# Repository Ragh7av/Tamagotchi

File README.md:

<h1 align="center">Tamagotchi</h1>

<div align="center">         
<p align="center">
Super smol tamagotchi pet for you!
</p>

<h1 align="center">Overview</h1>
        
<p align="center">
 
 Custom tamagotchi with a super small formfactor and can help you [larp](https://en.wiktionary.org/wiki/LARP) building hardware. Made using the good old ESP32 C3 Supermini, an 0.96 oled panel, three [smol](https://en.wiktionary.org/wiki/smol) tactile switches, buzzer, and a battery [ofc](https://en.wikipedia.org/wiki/OFC) with a custom PCB and a 3D printed case! 

 [Onshape 3D Model link](https://cad.onshape.com/documents/aaa376a98daf92ea29d656f5/w/34884ae89482b25306f22cdd/e/82753004b14a47683b19c43f)

 #  Schematic

# Printed Circuit Board (PCB)

# 3D MODEL OF ASSEMBLY

# ZINE

<h1 align="center">Why did I even build this?</h1>
<p align="center">
 
 to [larp](https://en.wiktionary.org/wiki/LARP) as a super smol cyberpet is cool [asf](https://en.wikipedia.org/wiki/Autism_Science_Foundation). 
 
 </p>

<h1 align="center">The Features</h1>
</div>

**Feeding:** Fills the hunger meter (much like a crunchy kfc) with sound effects

**Playing:** Yooo... Pauses the normal world to launch the falling-item arcade game. Catching items makes the pet superrrr happy but sadlyy acts as a 20% battery tax on its energy.

**Sleeping:** Dims the screen into a snoozee/ sleeping mode, locking the controls until its energy battery safely recharges back to 100% and get's into full powerr.

# The Components Used

1. ESP32 C3 supermini.
2. 0.96-inch OLED Display (SSD1306)
3. smol Buzzer.
4. 6mm x 6mm x 8mm Tactile Switches (x3).
5. Battery
7. Custom designes PCB.
8. Custom 3D Printed Case.

# How to Build it?
## 1. Project Files and Parts
Download the necessary files from this repository:
* Gerbers: For ordering the custom PCB.
* 3D Prints: For printing the outer case.
* Firmware: For the Arduino source code.

Now collect all the hardware components. You will need an ESP32-C3 Supermini, a 0.96-inch I2C OLED display, three 6mm tactile switches, a buzzer and a battery cell.
## 2. Hardware Assembly

To assemble the hardware follow these steps:
1. Solder the ESP32-C3 Supermini onto the designated footprint on your PCB.
2. Next solder the three switches into positions SW4, SW5 and SW6.
3. Then solder the OLED display into the U2 slot.
4. After that solder the buzzer to the BZ1 pads.
5. Solder the battery wires to the BT1 power pads. It is very important to check the schematic to ensure the positive and negative match exactly to prevent shorting out the ESP32-C3 Supermini board.
6. Finally, Place the PCB in the 3D printed bottom case and screw it to the case.

## 3. Software Environment Setup

To set up the software environment follow these steps:

1. Install the Arduino IDE on your computer.
3. Go to File then Preferences. Add the official ESP32 library URL to the Additional Boards Manager URLs box.
5. Open Tools, Board then Boards Manager, search for ESP32 by Expressif and click install.
6. Go back to Tools, Board, then ESP32 Arduino and select ESP32 C3 Dev Module.

## 4. Library Installation and Flashing

To install the library and flash the firmware follow these steps:

1. Go to Sketch Include Library then Manage Libraries.
2. Search for Adafruit SSD1306. Click install. Select "Install All" to include the required Adafruit GFX dependency.
3. Open your project firmware file in the Arduino IDE.
4. Connect the ESP32-C3 Supermini device to your computer using a data cable.
5. Select the devices connection port, under Tools, Port.
6. Click the Upload button. The OLED screen will boot up with the system text soon as the terminal finishes writing the code to the ESP32-C3 Supermini.
   
<h1>Inspirations & Credits</h1> 
Huge thanks to the <strong>Fallout Hack Club Tamagotchi guide</strong> for the base inspiration and logic outline.

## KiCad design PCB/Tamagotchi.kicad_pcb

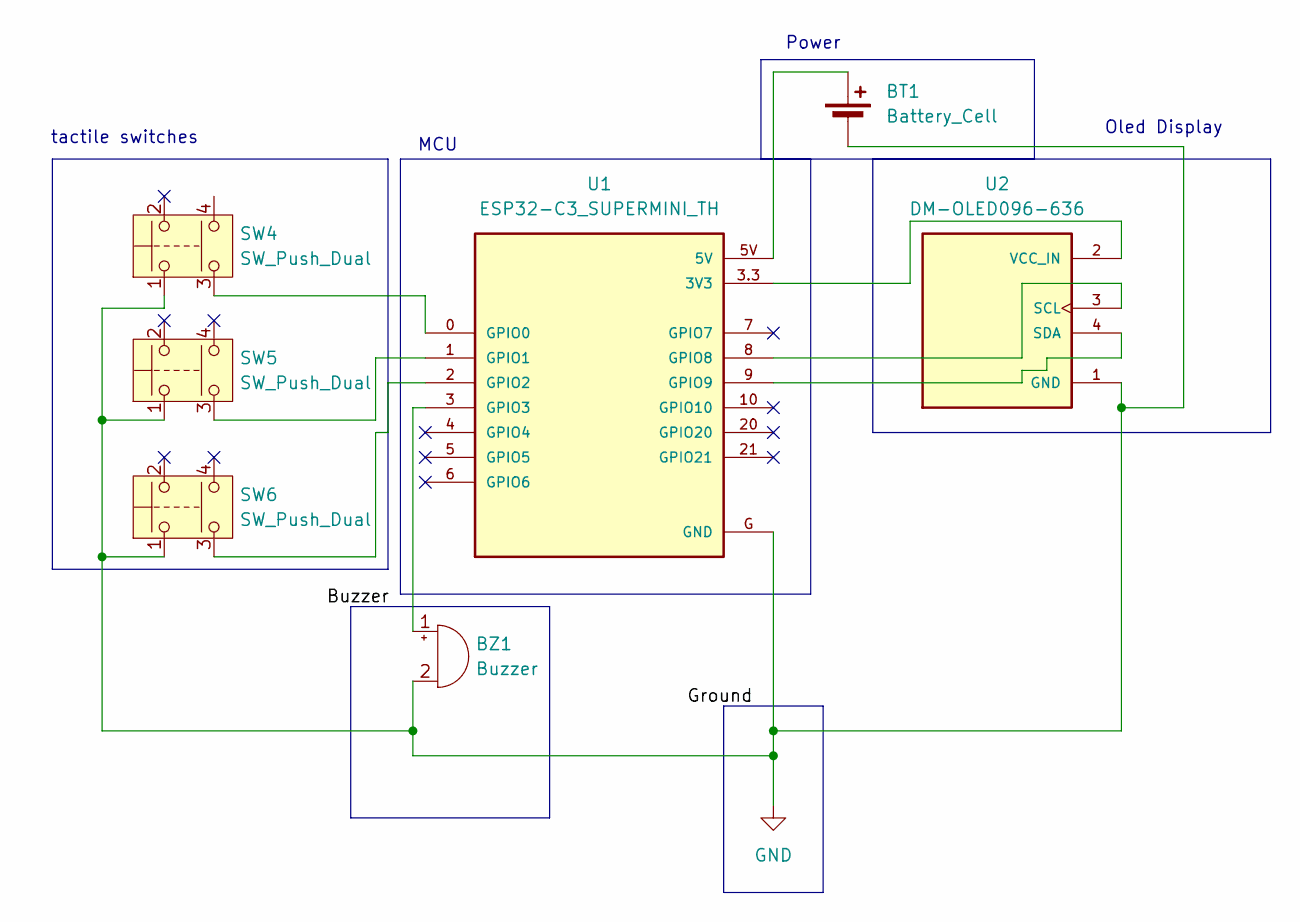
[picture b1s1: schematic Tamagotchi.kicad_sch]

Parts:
BT1: Battery_Cell; TE_282837-2
BZ1: Buzzer; BUZ-TH_BD9.6-P5.00-D0.6-FD_XHXDZ-TMB9650-5V
SW4, SW5, SW6: SW_Push_Dual; 430182043816
U1: ESP32-C3_SUPERMINI_TH; MODULE_ESP32-C3_SUPERMINI_TH
U2: DM-OLED096-636; 128x64OLED SSD1306; PARTREV 2018-09-10

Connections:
GND: BT1.2 (-), BZ1.2 (-), SW4.1, SW5.1, SW6.1, U1.G (GND), U2.1 (GND)
unnamed: BT1.1 (+), U1.5V
unnamed: BZ1.1 (+), U1.3 (GPIO3)
unnamed: U1.3.3 (3V3), U2.2 (VCC_IN)
unnamed: SW4.3, U1.0 (GPIO0)
unnamed: SW5.3, U1.1 (GPIO1)
unnamed: SW6.3, U1.2 (GPIO2)
unnamed: U1.8 (GPIO8), U2.3 (SCL)
unnamed: U1.9 (GPIO9), U2.4 (SDA)

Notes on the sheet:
MCU
tactile switches
Power
Oled Display

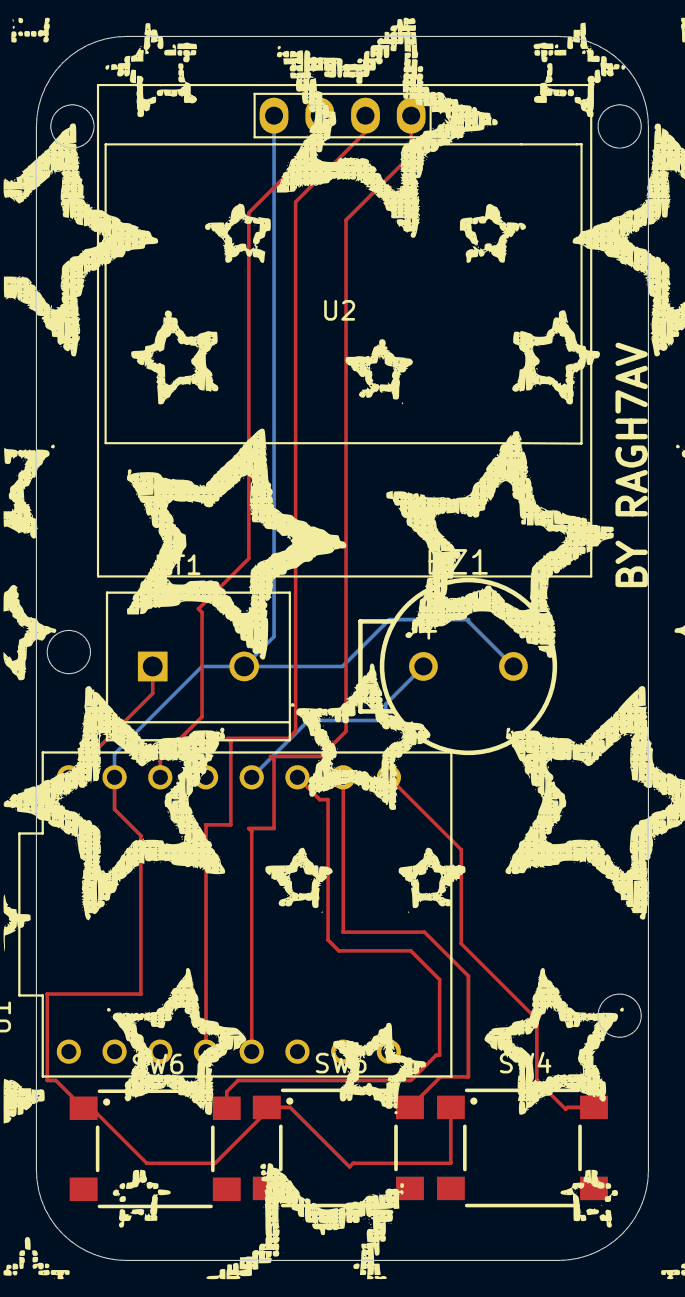
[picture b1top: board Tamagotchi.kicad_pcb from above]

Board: 2 copper layers, 34.0 x 68.0 mm, 7 parts (0 on the bottom side), 9 nets.

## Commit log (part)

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2026-06-20 Create idk cad
2026-06-20 Create NVM
2026-06-20 Create MEOW
2026-06-20 Create 3D_PRINTS
2026-06-20 Create BOM
2026-06-20 Create HEEHEEEE
2026-06-20 Create SWIM
2026-06-20 Create SWIFT
2026-06-20 Create UHHHHH
2026-06-25 Configure Git LFS for STP files
2026-06-25 Configure Git LFS for STEP, STP, and STL files
2026-06-25 Add Tamagotchi project files
2026-06-25 Create LOVE
2026-06-25 Create YEARN
2026-06-25 Create ZINE
